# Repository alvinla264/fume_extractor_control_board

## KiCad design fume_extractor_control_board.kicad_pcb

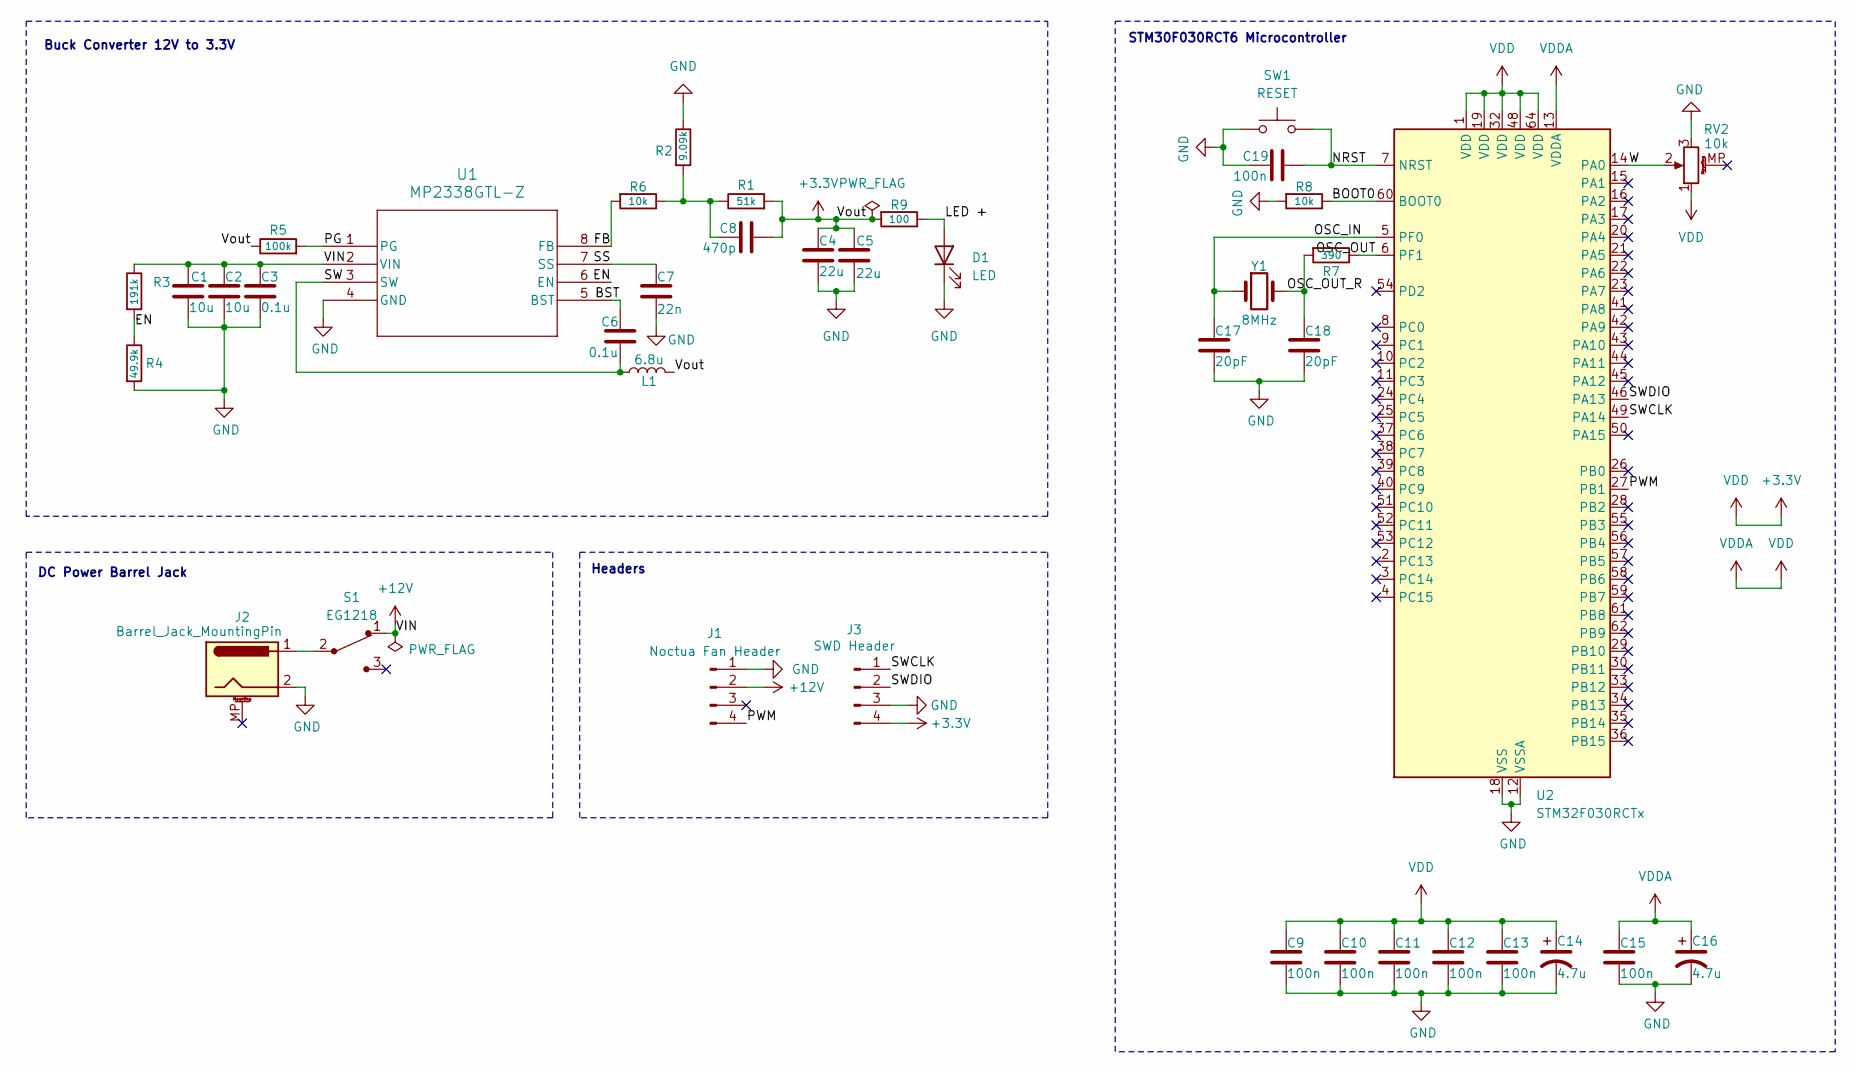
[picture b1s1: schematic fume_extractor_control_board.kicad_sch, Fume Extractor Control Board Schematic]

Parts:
C1, C2: 10u; C_0805_2012Metric_Pad1.18x1.45mm_HandSolder
C3, C6: 0.1u; C_0805_2012Metric_Pad1.18x1.45mm_HandSolder
C4, C5: 22u; C_0805_2012Metric_Pad1.18x1.45mm_HandSolder
C7: 22n; C_0805_2012Metric_Pad1.18x1.45mm_HandSolder
C8: 470p; C_0805_2012Metric_Pad1.18x1.45mm_HandSolder
C9, C10, C11, C12, C13, C15, C19: 100n; C_0805_2012Metric_Pad1.18x1.45mm_HandSolder
C14, C16: 4.7u; CP_Radial_D4.0mm_P1.50mm
C17, C18: 20pF; C_0805_2012Metric_Pad1.18x1.45mm_HandSolder
D1: LED; LED_0805_2012Metric_Pad1.15x1.40mm_HandSolder
J1: Noctua Fan Header; FanPinHeader_1x04_P2.54mm_Vertical
J2: Barrel_Jack_MountingPin; BarrelJack_Horizontal
J3: SWD Header; PinHeader_1x04_P2.54mm_Vertical
L1: 6.8u; L_0805_2012Metric_Pad1.05x1.20mm_HandSolder
R1: 51k; R_0805_2012Metric_Pad1.20x1.40mm_HandSolder
R2: 9.09k; R_0805_2012Metric_Pad1.20x1.40mm_HandSolder
R3: 191k; R_0805_2012Metric_Pad1.20x1.40mm_HandSolder
R4: 49.9k; R_0805_2012Metric_Pad1.20x1.40mm_HandSolder
R5: 100k; R_0805_2012Metric_Pad1.20x1.40mm_HandSolder
R6, R8: 10k; R_0805_2012Metric_Pad1.20x1.40mm_HandSolder
R7: 390; R_0805_2012Metric_Pad1.20x1.40mm_HandSolder
R9: 100; R_0805_2012Metric_Pad1.20x1.40mm_HandSolder
RV2: 10k; Potentiometer_P120PK-Y25BR10K
S1: EG1218; Switch_Slide_11.6x4mm_EG1218; MPN EG1218; Digi-Key_PN EG1903-ND
SW1: RESET; SW_PUSH_6mm
U1: MP2338GTL-Z; SOT583_MP2338_MNP
U2: STM32F030RCTx; LQFP-64_10x10mm_P0.5mm
Y1: 8MHz; Crystal_HC49-4H_Vertical

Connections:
+3.3V: C4.1, C5.2, C8.2, C9.1, C10.1, C11.1, C12.1, C13.1, C14.1, C15.1, C16.1, J3.4, L1.2, R1.2, R5.1, R9.2, RV2.1, U2.1 (VDD), U2.13 (VDDA), U2.19 (VDD), U2.32 (VDD), U2.48 (VDD), U2.64 (VDD)
+12V: C1.1, C2.1, C3.1, J1.2, R3.1, S1.1, U1.2 (VIN)
/BOOT0: R8.1, U2.60 (BOOT0)
/BST: C6.1, U1.5 (BST)
/EN: R3.2, R4.1, U1.6 (EN)
/FB: R6.2, U1.8 (FB)
/LED +: D1.2 (A), R9.1
/NRST: C19.2, SW1.2, U2.7 (NRST)
/OSC_IN: C17.1, U2.5 (PF0), Y1.1
/OSC_OUT: R7.1, U2.6 (PF1)
/OSC_OUT_R: C18.1, R7.2, Y1.2
/PG: R5.2, U1.1 (PG)
/PWM: J1.4, U2.27 (PB1)
/SS: C7.1, U1.7 (SS)
/SW: C6.2, L1.1, U1.3 (SW)
/SWCLK: J3.1, U2.49 (PA14)
/SWDIO: J3.2, U2.46 (PA13)
/W: RV2.2, U2.14 (PA0)
GND: C1.2, C2.2, C3.2, C4.2, C5.1, C7.2, C9.2, C10.2, C11.2, C12.2, C13.2, C14.2, C15.2, C16.2, C17.2, C18.2, C19.1, D1.1 (K), J1.1, J2.2, J3.3, R2.1, R4.2, R8.2, RV2.3, SW1.1, U1.4 (GND), U2.12 (VSSA), U2.18 (VSS), U2.31 (VSS), U2.47 (VSS), U2.63 (VSS)
unnamed: C8.1, R1.1, R2.2, R6.1
unnamed: J2.1, S1.2

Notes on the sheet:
Buck Converter 12V to 3.3V
DC Power Barrel Jack
STM30F030RCT6 Microcontroller
Headers

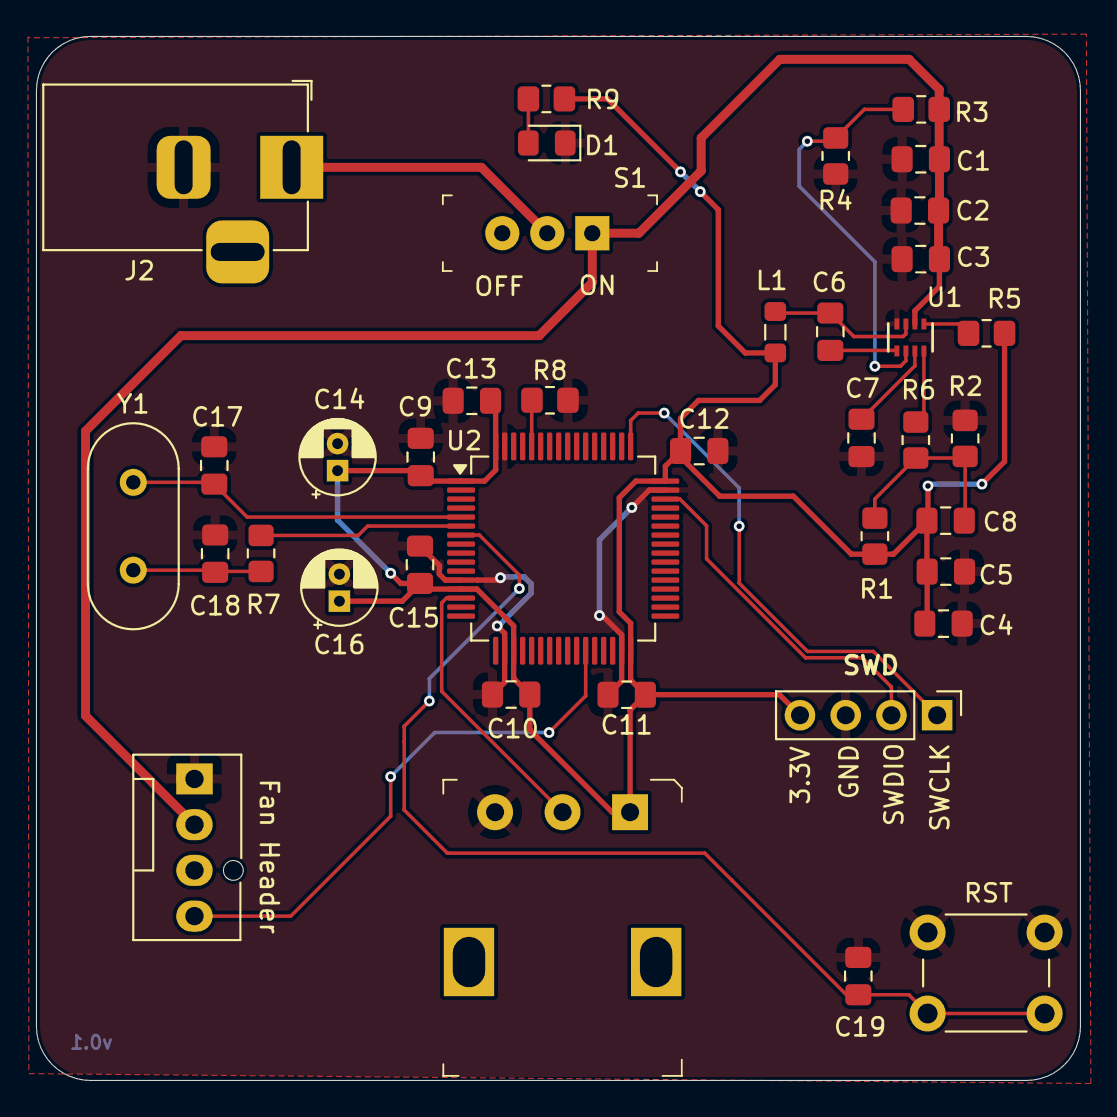
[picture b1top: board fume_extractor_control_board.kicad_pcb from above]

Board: 2 copper layers, 58.0 x 58.0 mm, 39 parts (0 on the bottom side), 21 nets.

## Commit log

2025-06-19 Initial Commit of KiCad Project
2025-06-19 updated gitignore
2025-06-19 Adjusted some traces
2025-06-19 changed and generated gerber
